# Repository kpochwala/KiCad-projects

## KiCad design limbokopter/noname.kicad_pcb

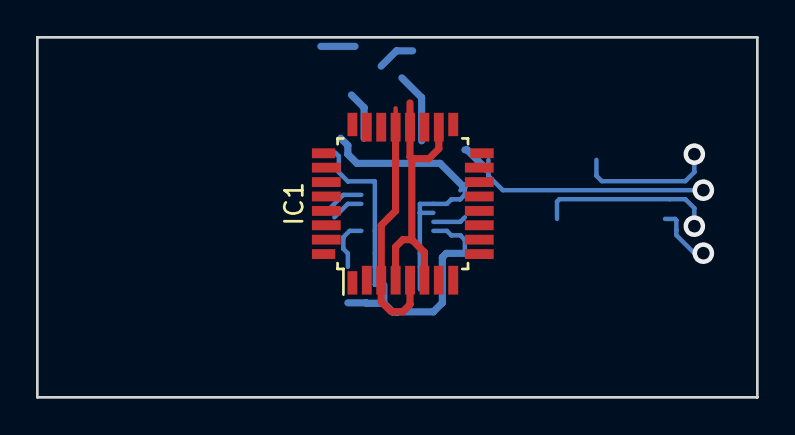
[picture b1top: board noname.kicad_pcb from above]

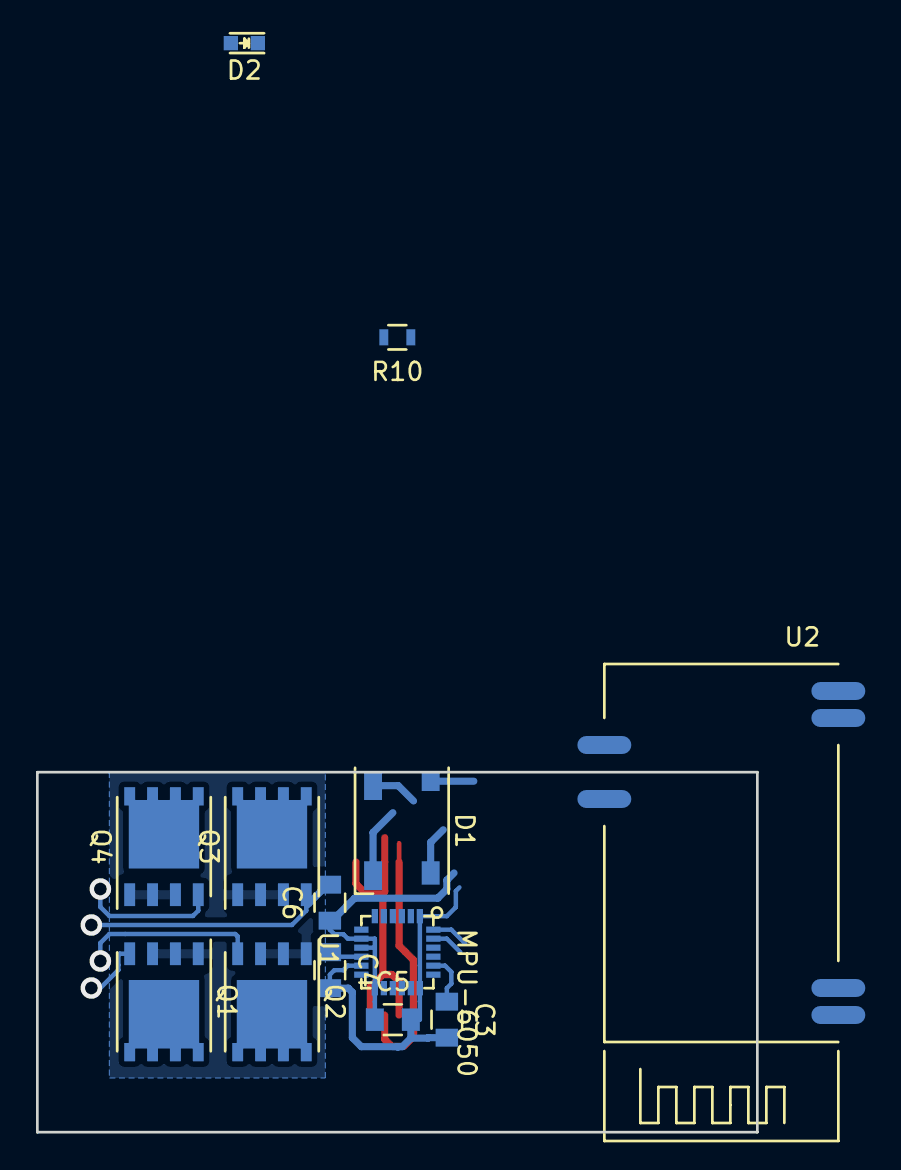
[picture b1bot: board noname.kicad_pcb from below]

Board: 2 copper layers, 40.0 x 20.0 mm, 14 parts (13 on the bottom side), 18 nets.

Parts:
C3: 2n2; C_0805
C4, C6: 0u1; C_0805
C5: 10n; C_0805
D1: Led_RGB_CA; LED_WS2812B-PLCC4
D2: LED; LED_0603
IC1: ATMEGA328-A; TQFP-32_7x7mm_Pitch0.8mm
Q1, Q2, Q3, Q4: IRF7607PBF; SO-8_PowerPAK_Vishay_Single
R10: R; R_0603
U1: MPU-6050
U2: HC06; HC06-minimal

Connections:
+3V3: C5.1, C6.1, IC1.4, IC1.6, IC1.18, IC1.20, U1.8, U1.9, U1.13, U2.12
/Bluetooth/RXD: IC1.31, U2.2
/IMU/SCL: IC1.28, U1.23
/IMU/SDA: IC1.27, U1.24
/Microcontroller/8_LED: D1.3, IC1.12
/Microcontroller/11_PWM_LEDA: D1.1, IC1.15
/Microcontroller/12_LED: D1.2, IC1.16
/Microcontroller/13_LED: D1.4, IC1.17
/Microcontroller/RXD: IC1.30, U2.1
/motor/M1: IC1.9, Q1.4
/motor/M2: IC1.10, Q2.4
/motor/M3: IC1.13, Q3.4
/motor/M4: IC1.14, Q4.4
GND: C3.2, C4.2, C5.2, C6.2, IC1.3, IC1.5, IC1.21, Q1.1, Q1.2, Q1.3, Q2.1, Q2.2, Q2.3, Q3.1, Q3.2, Q3.3, Q4.1, Q4.2, Q4.3, R10.2, U1.1, U1.11, U1.18, U2.13, U2.26
unnamed: C3.1, U1.20
unnamed: C4.1, U1.10
unnamed: D2.1, R10.1
unnamed: D2.2, U2.24

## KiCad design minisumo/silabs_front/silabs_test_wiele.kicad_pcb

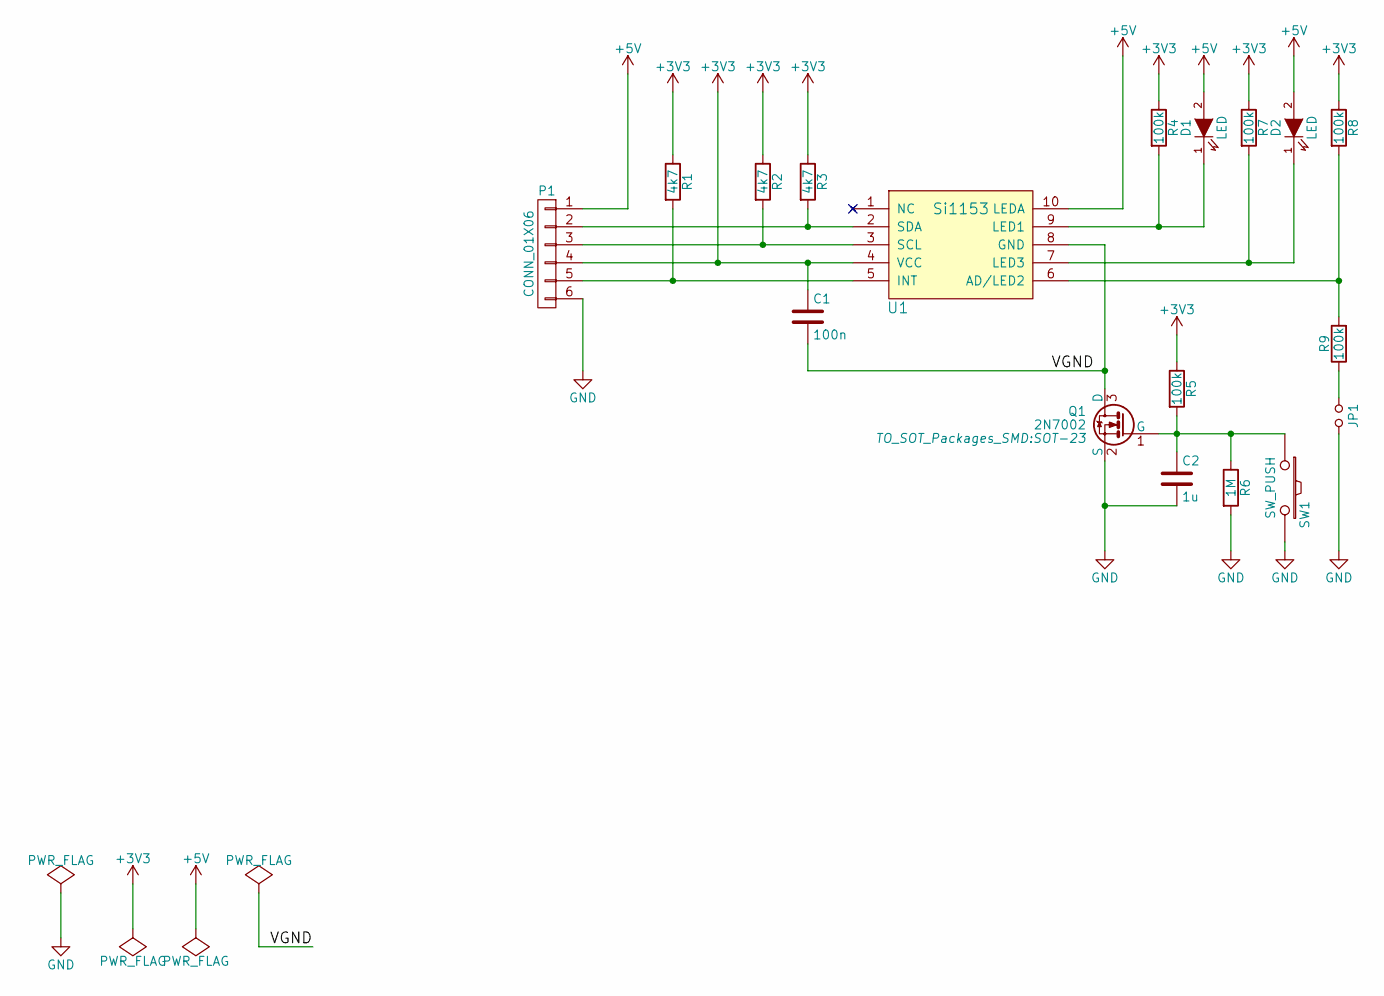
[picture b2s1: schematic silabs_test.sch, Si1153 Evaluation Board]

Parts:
C1: 100n; C_0603_HandSoldering
C2: 1u; C_0805_HandSoldering
D1, D2: LED; MiniMELF_Standard
JP1: Jumper_NO_Small; R_0201
P1: CONN_01X06
Q1: 2N7002; SOT-23
R1, R2, R3: 4k7; R_0805
R4, R5, R7, R8, R9: 100k; R_0805
R6: 1M; R_0805
SW1: SW_PUSH; SW_SPST_FSMSM
U1: Si1153

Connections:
+3V3: C1.1, P1.4, R1.1, R2.1, R3.1, R4.1, R5.1, R7.1, R8.1, U1.4 (VCC)
+5V: D1.2 (A), D2.2 (A), P1.1, U1.10 (LEDA)
GND: C2.2, JP1.2, P1.6, Q1.2 (S), R6.2, SW1.2
unnamed: C1.2, Q1.3 (D), U1.8 (GND)
unnamed: C2.1, Q1.1 (G), R5.2, R6.1, SW1.1
unnamed: D1.1 (K), R4.2, U1.9 (LED1)
unnamed: D2.1 (K), R7.2, U1.7 (LED3)
unnamed: JP1.1, R9.1
unnamed: P1.2, R3.2, U1.2 (SDA)
unnamed: P1.3, R2.2, U1.3 (SCL)
unnamed: P1.5, R1.2, U1.5 (INT)
unnamed: R8.2, R9.2, U1.6 (AD/LED2)

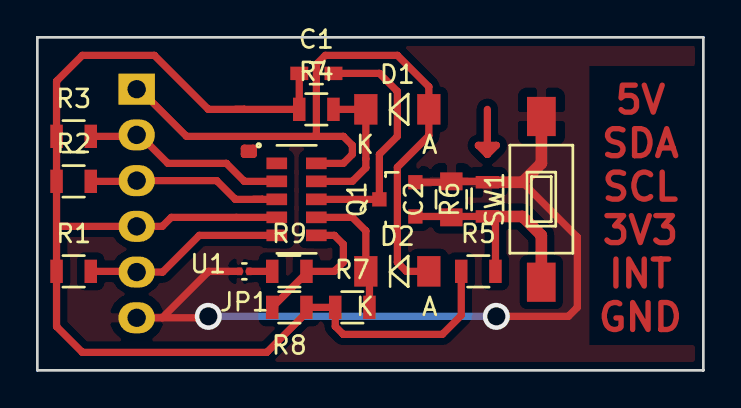
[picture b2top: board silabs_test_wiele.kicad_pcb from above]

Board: 2 copper layers, 37.0 x 18.5 mm, 18 parts (1 on the bottom side), 12 nets.
